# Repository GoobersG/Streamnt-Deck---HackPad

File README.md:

# Hackpad

A custom DIY macro pad inspired by (but not at all) Stream Deck.

This project is a small hardware controller built around the **Seeed XIAO RP2040**, featuring:
- 6× Cherry MX mechanical switches  
- 1× EC11 rotary encoder  
- 1× 0.91" SSD1306 OLED display (I2C)  
- A fully custom PCB (KiCad)  
- A 3D-printed snug-fit case

Designed and built as a Hack Club hardware project.

---

## Hardware Overview

- **MCU:** Seeed Studio XIAO RP2040 (DIP)
- **Switches:** Cherry MX compatible (6 total)
- **Encoder:** EC11 rotary encoder
- **Display:** SSD1306 OLED, 0.91", 128×32, I2C (4-pin)
- **Power:** USB-C via XIAO
- **Enclosure:** 3D printed (top + bottom)

---

## Pin Mapping

### Switches
| Switch | Function | XIAO Pin |
|------|--------|---------|
| SW1 | Key 1 | GPIO26 |
| SW2 | Key 2 | GPIO2 |
| SW3 | Key 3 | GPIO1 |
| SW4 | Key 4 | GPIO27 |
| SW5 | Key 5 | GPIO3 |
| SW6 | Key 6 | GPIO4 |

### Rotary Encoder
| Signal | XIAO Pin |
|------|---------|
| Encoder A | GPIO28 |
| Encoder B | GPIO29 |
| Encoder C | GND |

### OLED (SSD1306, I2C)
| Signal | XIAO Pin |
|------|---------|
| SDA | GPIO5 |
| SCL | GPIO6 |
| VCC | 3V3 |
| GND | GND |

---

### PCB
- KiCad project files (`.kicad_sch`, `.kicad_pcb`, `.kicad_pro`)
- Gerbers and drill files for manufacturing
- PDF exports of schematic and PCB
- STEP file for enclosure design

## PCB Images

### Case
- Fusion 360 design file
- STL files for:
  - `case_top.stl`
  - `case_bottom.stl`
-STEP files for:
  - `case_bottom.step`
  - `case_top.step`
  - `hackpad_case_assembly.step`

---

## Case Design Notes

- 3 mm walls and bottom thickness
- Internal snup-fit using wall thickness
- PCB is fully supported without mounting holes
- Designed for FDM printing (PLA+ / PETG recommended)

## Case Images

---

## Build Instructions (High Level)

1. Order PCB using the Gerbers in `hardware/kicad/fabrication/`
2. Solder:
   - Switches
   - Encoder
   - OLED header
3. Plug in XIAO RP2040
4. 3D print the case (STLs in `case/stl/`)
5. Assemble PCB into bottom case
6. Snap on top case
7. Flash firmware (see `firmware/`)

---

## Status

- Hardware: ✅ complete  
- PCB: ✅ routed and exported  
- Case: ✅ designed and printable  
- Firmware: Demo Ready

---

## License

MIT License — feel free to learn from, modify, and build on this project.

---

**STREAMN’T DECK**

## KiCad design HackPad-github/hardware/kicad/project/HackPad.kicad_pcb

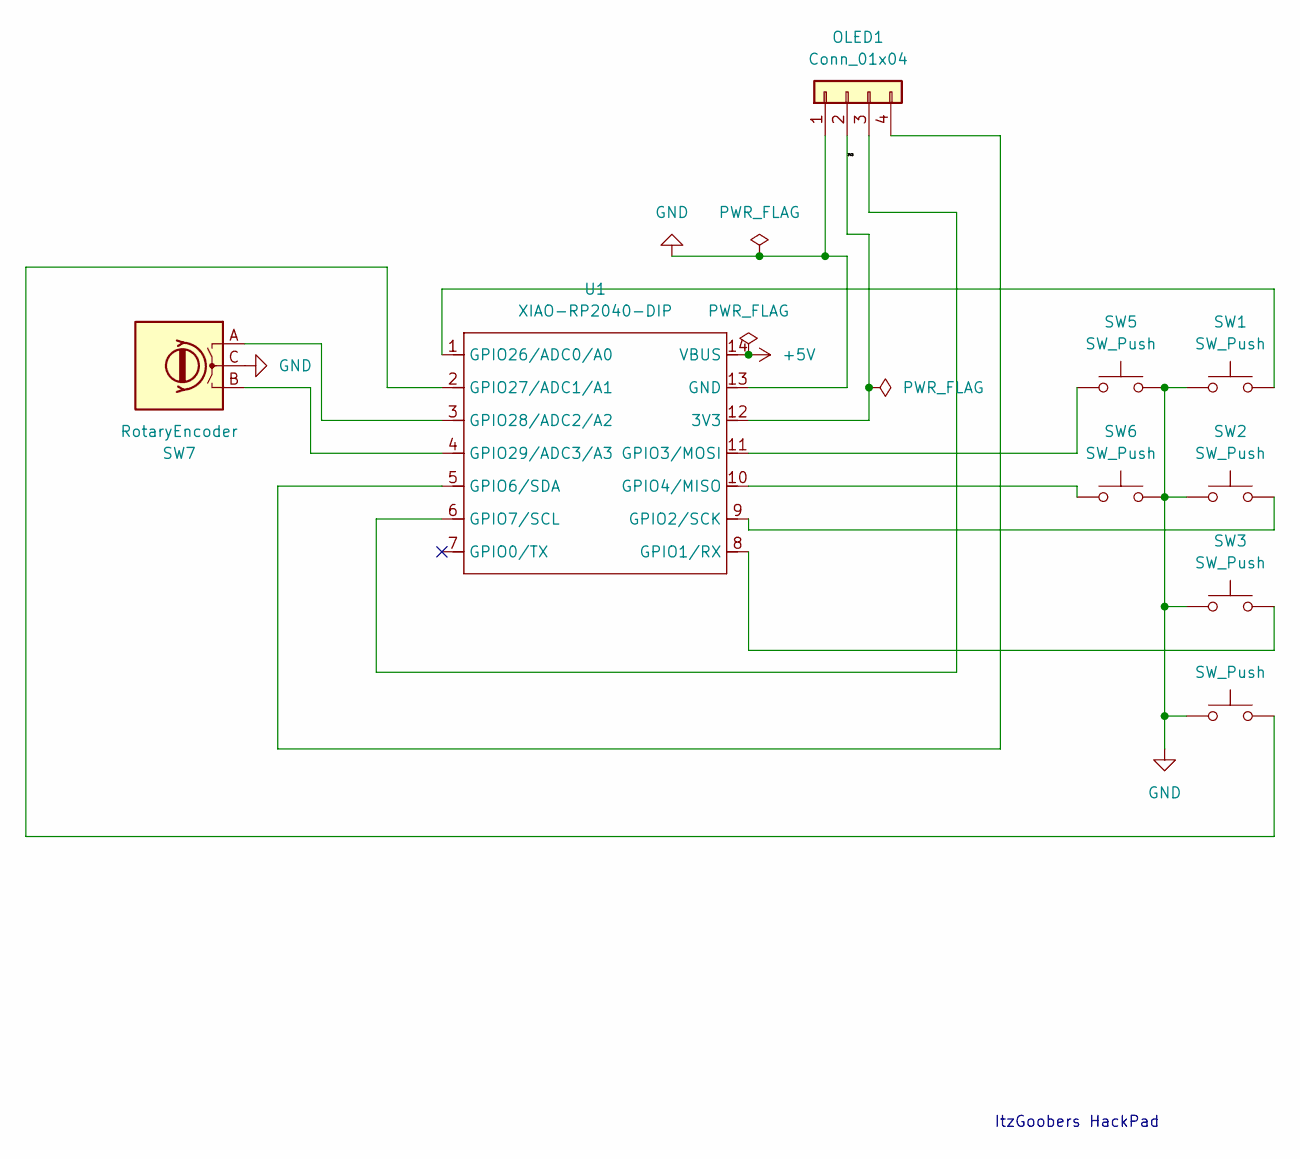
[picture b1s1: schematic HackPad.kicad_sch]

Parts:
OLED1: Conn_01x04; SSD1306-0.91-OLED-4pin-128x32
SW1, SW2, SW3, SW4, SW5, SW6: SW_Push; SW_Cherry_MX_1.00u_PCB
SW7: RotaryEncoder; RotaryEncoder_Alps_EC11E_Vertical_H20mm
U1: XIAO-RP2040-DIP

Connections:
+5V: U1.14 (VBUS)
/3V3: OLED1.2 (VCC), U1.12 (3V3)
GND: OLED1.1 (GND), SW1.1, SW2.1, SW3.1, SW4.1, SW5.2, SW6.2, SW7.C, U1.13 (GND)
unnamed: OLED1.3 (SCL), U1.6 (GPIO7/SCL)
unnamed: OLED1.4 (SDA), U1.5 (GPIO6/SDA)
unnamed: SW3.2, U1.8 (GPIO1/RX)
unnamed: SW2.2, U1.9 (GPIO2/SCK)
unnamed: SW5.1, U1.11 (GPIO3/MOSI)
unnamed: SW6.1, U1.10 (GPIO4/MISO)
unnamed: SW1.2, U1.1 (GPIO26/ADC0/A0)
unnamed: SW4.2, U1.2 (GPIO27/ADC1/A1)
unnamed: SW7.A, U1.3 (GPIO28/ADC2/A2)
unnamed: SW7.B, U1.4 (GPIO29/ADC3/A3)

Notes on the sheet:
ItzGoobers HackPad

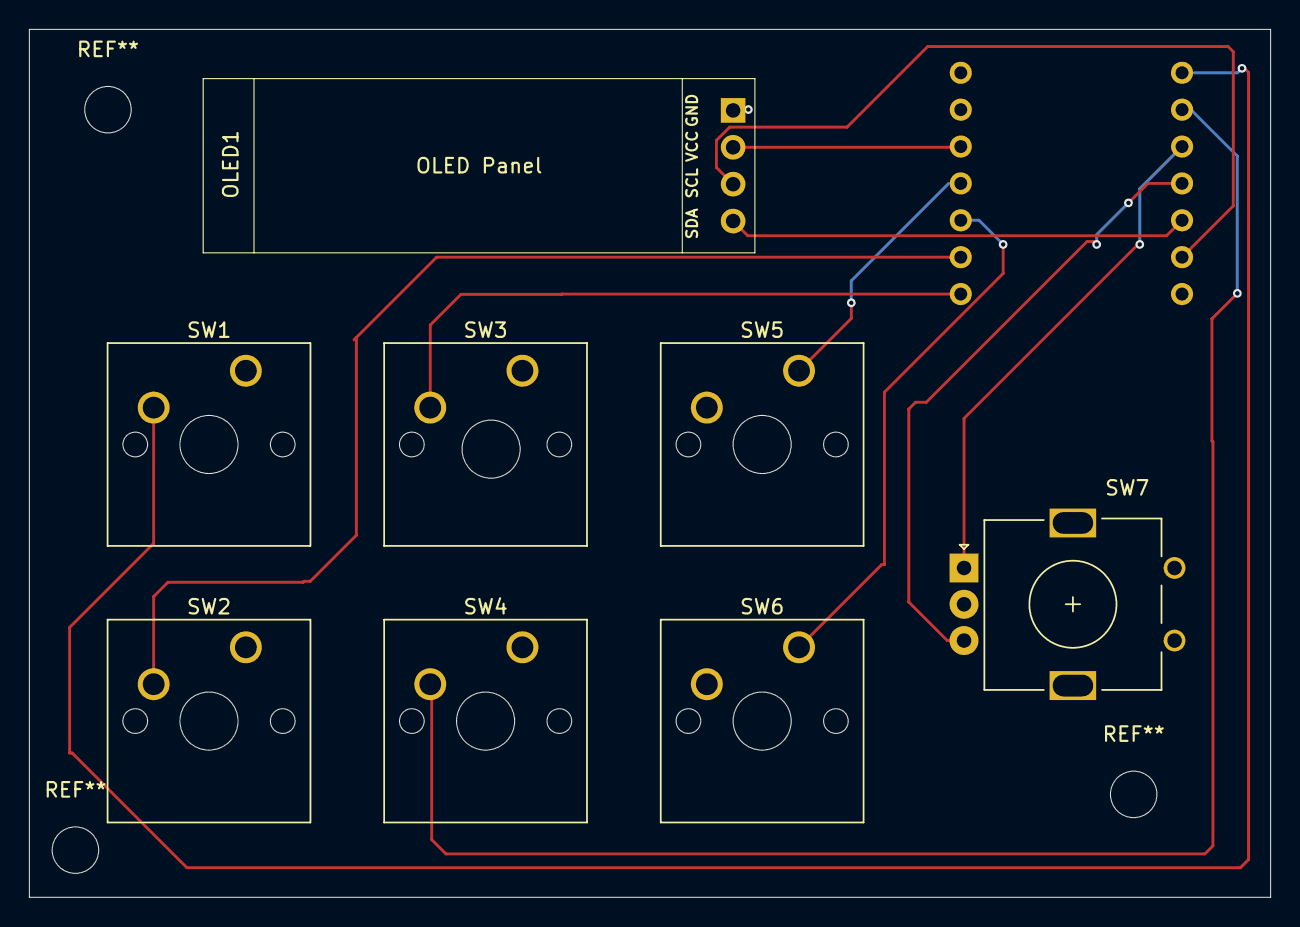
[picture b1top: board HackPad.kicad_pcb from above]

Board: 2 copper layers, 85.5 x 59.8 mm, 9 parts (1 on the bottom side), 12 nets.

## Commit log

2026-01-16 Add initial README for Hackpad project
2026-01-17 Include STEP files for case design
    Added STEP files for case components.
2026-01-17 Add PCB and case images to README
    Added images for PCB and case to the README.
2026-01-17 Fix image paths in README.md
    Updated image paths in README.md to use forward slashes.
2026-01-17 Update firmware status to 'Demo Ready'
